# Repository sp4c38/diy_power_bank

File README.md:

# DIY Power Bank

This repository contains the project files for my custom power bank, including the PCB design and fabrication files, firmware, iOS app, and 3D-printable enclosure parts.

The files are provided for anyone interested in the project or who wants to learn from it. This is not a complete step-by-step build guide.

[Project showcase](https://www.space8.me/custom-power-bank.html)

Lithium-ion batteries can be dangerous. The files are provided as-is and should only be used with appropriate knowledge and safety precautions.

## License

This project is available under the [MIT License](LICENSE).

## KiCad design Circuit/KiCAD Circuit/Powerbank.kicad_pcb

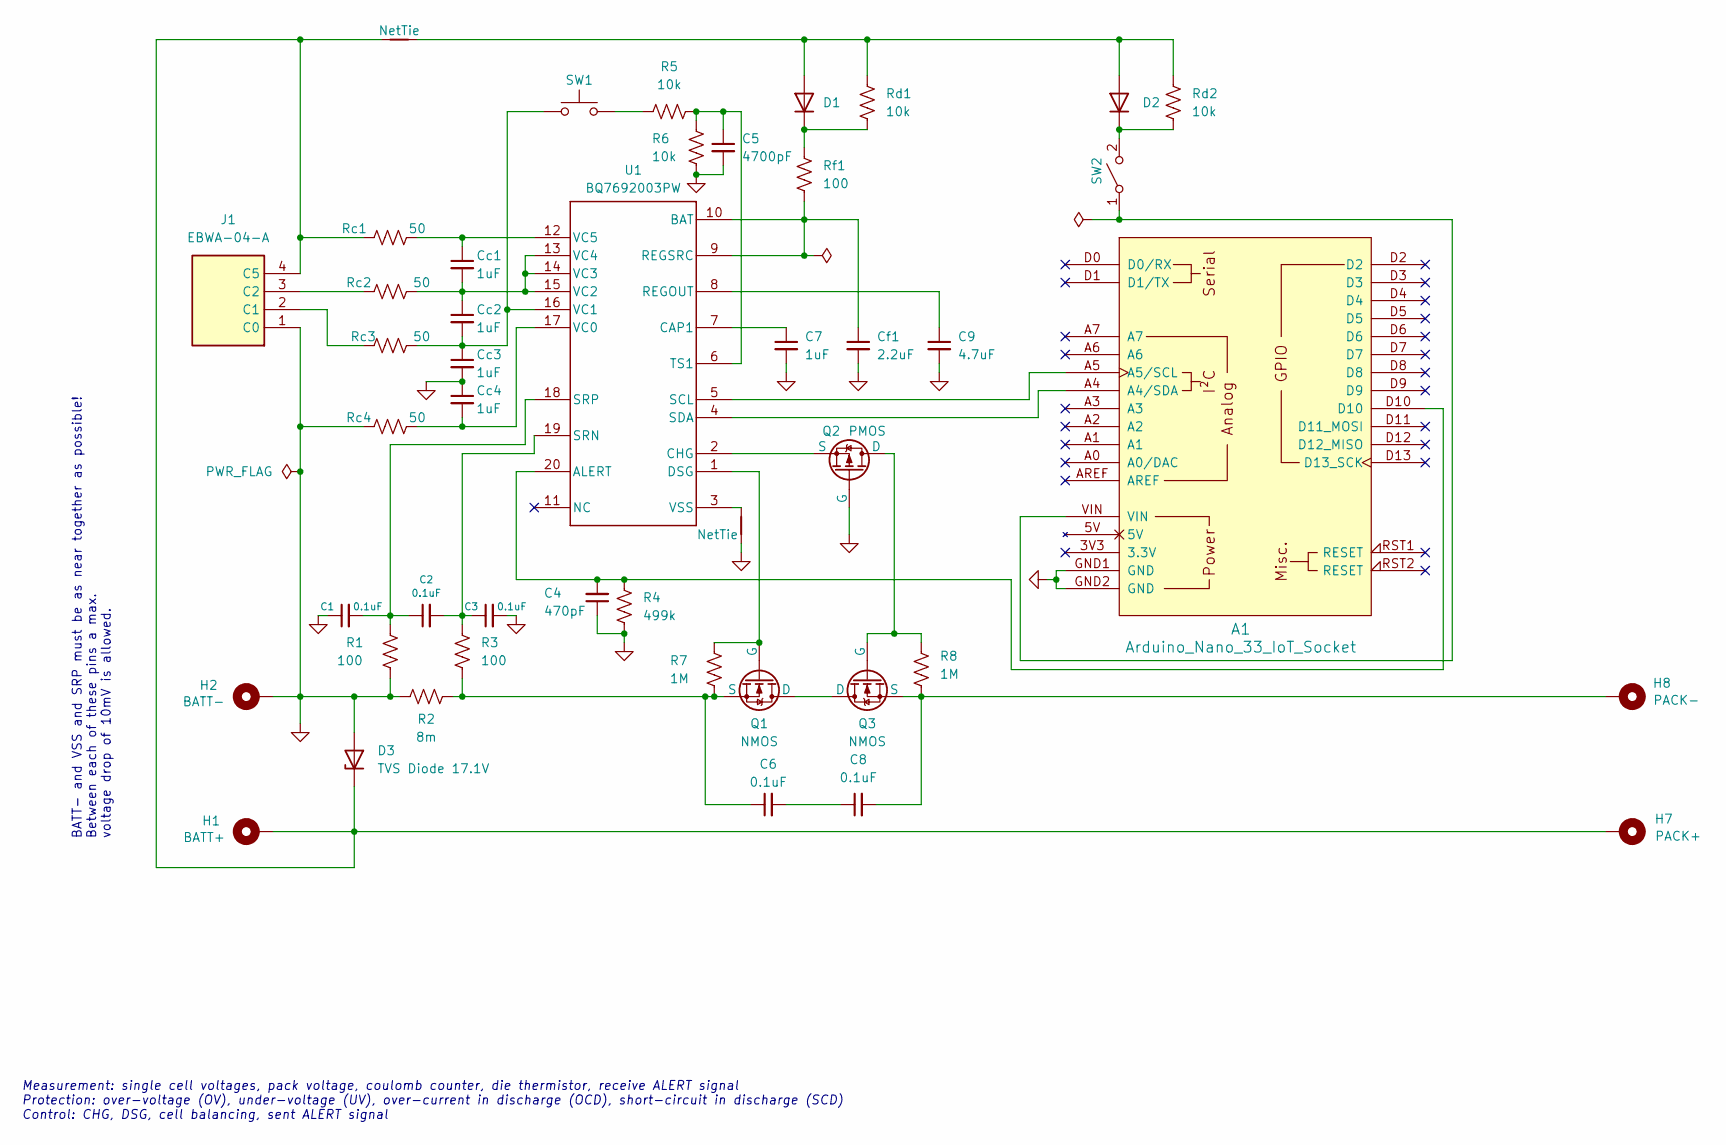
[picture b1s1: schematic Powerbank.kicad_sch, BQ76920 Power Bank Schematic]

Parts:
A1: Arduino_Nano_33_IoT_Socket
C1, C2, C3, C6, C8: 0.1uF; K104K10X7RF53H5_VIS; Mouser 594-K104K10X7RF53H5
C4: 470pF; K471K10X7RF5UH5_VIS; Mouser 594-K471K10X7RF5UH5
C5: 4700pF; CAP_C410C_AX_X7R_AXIMAX_KEM; Mouser 80-C410C472K1R
C7: 1uF; K105K20X7RF5TH5_VIS; Mouser 594-K105K20X7RF5TH5
C9: 4.7uF; CAP_FG24_TDK; Mouser 810-FG24X7R1E475KRT6
Cc1, Cc2, Cc3, Cc4: 1uF; K105K20X7RF5TH5_VIS; Mouser 594-K105K20X7RF5TH5
Cf1: 2.2uF; CAP_FG18_TDK; Mouser 810-FG18X5R1E225KRT6
D1, D2: D; 1N4149TR; Mouser 512-1N4149
D3: TVS Diode 17.1V; D_DO-41_SOD81_P7.62mm_Horizontal; Mouser 576-P4KE20A
H1: BATT+; Power Connection Pads
H2: BATT-; Power Connection Pads
H7: PACK+; Power Connection Pads
H8: PACK-; Power Connection Pads
J1: EBWA-04-A; Manufacturer_Part_Number EBWA-04-A; Mouser 737-EBWA-04-A
NT1, NT2: NetTie; NetTie General Net Class
Q1, Q3: NMOS; IRLB4132PBF; Mouser 942-IRLB4132PBF
Q2: PMOS; TO-92_MC_MCH; Mouser 689-VP3203N3-G
R1, R3: 100; STA_RNF14_STP; Mouser 708-RNF14FTD100R
R2: 8m; RES_14A_OHM; Mouser 588-14AFR008E
R4: 499k; YAG_MF25_YAG; Mouser 603-MFR-25FBF52-499K
R5, R6: 10k; STA_RNF18_STP; Mouser 708-RNF18FTD10K0
R7, R8: 1M; YAG_MF25_YAG; Mouser 603-MFR-25FRF521M
Rc1, Rc2, Rc3, Rc4: 50; RES_CMF07_VIS; Mouser 71-CMF5550R000FKEK70
Rd1, Rd2: 10k; STA_RNF18_STP; Mouser 708-RNF18FTD10K0
Rf1: 100; STA_RNF14_STP; Mouser 708-RNF14FTD100R
SW1: SW_Push; Switch Pads
SW2: SW_SPST; Switch Pads
U1: BQ7692003PW; PW0020A_N; Mouser 595-BQ7692003PW

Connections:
GND: A1.GND1 (GND), A1.GND2 (GND), C1.1, C3.2, C4.1, C5.2, C7.2, C9.2, Cc3.2, Cc4.1, Cf1.2, D3.2 (A), H2.1, J1.1 (C0), NT2.1, Q2.2 (G), R1.2, R2.1, R4.2, R6.2, Rc4.1
unnamed: A1.A4 (A4/SDA), U1.4 (SDA)
unnamed: A1.A5 (A5/SCL), U1.5 (SCL)
unnamed: C6.2, C8.1
unnamed: D1.2 (A), D2.2 (A), NT1.2, Rd1.1, Rd2.1
unnamed: D1.1 (K), Rd1.2, Rf1.1
unnamed: D2.1 (K), Rd2.2, SW2.2 (B)
unnamed: D3.1 (K), H1.1, H7.1, J1.4 (C5), NT1.1, Rc1.1
unnamed: J1.2 (C1), Rc3.1
unnamed: J1.3 (C2), Rc2.1
unnamed: Q1.1 (D), Q3.1 (D)
unnamed: Q1.2 (G), R7.1, U1.1 (DSG)
unnamed: C6.1, Q1.3 (S), R2.2, R3.2, R7.2
unnamed: Q2.1 (D), Q3.2 (G), R8.1
unnamed: Q2.3 (S), U1.2 (CHG)
unnamed: C8.2, H8.1, Q3.3 (S), R8.2
unnamed: R5.1, SW1.2
unnamed: A1.VIN, SW2.1 (A)
unnamed: A1.D10, C4.2, R4.1, U1.20 (ALERT)
unnamed: Cf1.1, Rf1.2, U1.9 (REGSRC), U1.10 (BAT)
unnamed: C7.1, U1.7 (CAP1)
unnamed: C9.1, U1.8 (REGOUT)
unnamed: C2.2, C3.1, R3.1, U1.19 (SRN)
unnamed: C1.2, C2.1, R1.1, U1.18 (SRP)
unnamed: C5.1, R5.2, R6.1, U1.6 (TS1)
unnamed: Cc4.2, Rc4.2, U1.17 (VC0)
unnamed: Cc2.2, Cc3.1, Rc3.2, SW1.1, U1.16 (VC1)
unnamed: Cc1.2, Cc2.1, Rc2.2, U1.13 (VC4), U1.14 (VC3), U1.15 (VC2)
unnamed: Cc1.1, Rc1.2, U1.12 (VC5)
unnamed: NT2.2, U1.3 (VSS)

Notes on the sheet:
BATT- and VSS and SRP must be as near together as possible! Between each of these pins a max. voltage drop of 10mV is allowed.
Measurement: single cell voltages, pack voltage, coulomb counter, die thermistor, receive ALERT signal Protection: over-voltage (OV), under-voltage (UV), over-current in discharge (OCD), short-circuit in discharge (SCD) Control: CHG, DSG, cell balancing, sent ALERT signal

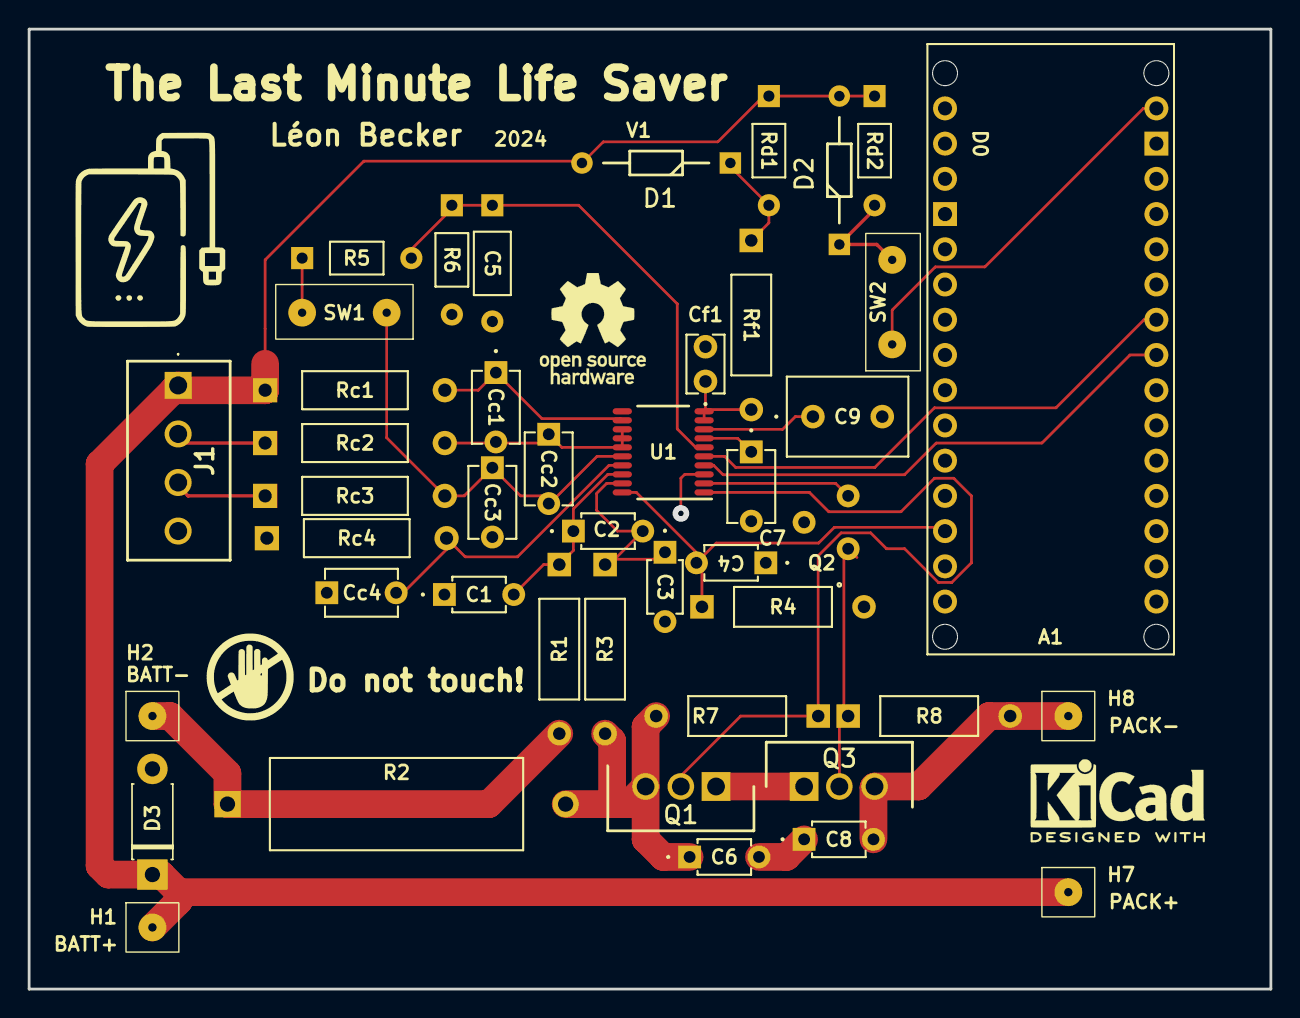
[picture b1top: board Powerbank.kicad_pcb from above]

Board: 2 copper layers, 89.5 x 69.2 mm, 49 parts (0 on the bottom side), 30 nets.

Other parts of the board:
G1: LOGO; Do Not Touch Symbol
G2: OSHW-Logo_7.5x8mm_SilkScreen
REF1: KiCad-Logo2_5mm_SilkScreen

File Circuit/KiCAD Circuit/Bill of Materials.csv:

"Reference","Value","Footprint","Qty","DNP","Mouser"
"A1","Arduino_Nano_33_IoT_Socket","Arduinos:Arduino_Nano_33_IoT_Socket","1","",""
"C1,C2,C3,C6,C8","0.1uF","K104K10X7RF53H5:K104K10X7RF53H5_VIS","5","","594-K104K10X7RF53H5"
"C4","470pF","K471K10X7RF5UH5:K471K10X7RF5UH5_VIS","1","","594-K471K10X7RF5UH5"
"C5","4700pF","C410C472K1R5TA:CAP_C410C_AX_X7R_AXIMAX_KEM","1","","80-C410C472K1R"
"C7,Cc1,Cc2,Cc3,Cc4","1uF","K105K20X7RF5TH5:K105K20X7RF5TH5_VIS","5","","594-K105K20X7RF5TH5"
"C9","4.7uF","FG24X7R1E475KRT06:CAP_FG24_TDK","1","","810-FG24X7R1E475KRT6"
"Cf1","2.2uF","FG18X5R1E225KRT06:CAP_FG18_TDK","1","","810-FG18X5R1E225KRT6"
"D1,D2","D","Custom Footprints:1N4149TR","2","","512-1N4149"
"D3","TVS Diode 17.1V","Diode_THT:D_DO-41_SOD81_P7.62mm_Horizontal","1","","576-P4KE20A"
"H1","BATT+","Custom Footprints:Power Connection Pads","1","",""
"H2","BATT-","Custom Footprints:Power Connection Pads","1","",""
"H7","PACK+","Custom Footprints:Power Connection Pads","1","",""
"H8","PACK-","Custom Footprints:Power Connection Pads","1","",""
"J1","EBWA-04-A","Custom Footprints:EBWA-04-A","1","","737-EBWA-04-A"
"Q1,Q3","NMOS","Custom Footprints:IRLB4132PBF","2","","942-IRLB4132PBF"
"Q2","PMOS","Custom Footprints:TO-92_MC_MCH","1","","689-VP3203N3-G"
"R1,R3,Rf1","100","RNF14FTD100R:STA_RNF14_STP","3","","708-RNF14FTD100R"
"R2","8m","14AFR008E:RES_14A_OHM","1","","588-14AFR008E"
"R4","499k","MFR-25FBF52-499K:YAG_MF25_YAG","1","","603-MFR-25FBF52-499K"
"R5,R6,Rd1,Rd2","10k","RNF18FTD10K0:STA_RNF18_STP","4","","708-RNF18FTD10K0"
"R7,R8","1M","MFR-25FRF52-1M:YAG_MF25_YAG","2","","603-MFR-25FRF521M"
"Rc1,Rc2,Rc3,Rc4","50","CMF5550R000FKEK70:RES_CMF07_VIS","4","","71-CMF5550R000FKEK70"
"SW1","SW_Push","Custom Footprints:Switch Pads","1","",""
"SW2","SW_SPST","Custom Footprints:Switch Pads","1","",""
"U1","BQ7692003PW","BQ7692003PW:PW0020A_N","1","","595-BQ7692003PW"

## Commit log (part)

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2023-12-29 Backup
2024-03-12 Ordered
2024-03-31 Fixed use of keyword "register"
2024-04-01 Backup 2
2024-04-01 Added CRC
2024-04-05 Added many software features (wip)
2024-04-11 Added balancing algorithm
2024-04-17 Backup (PlatformIO)
2024-06-26 Changed limits
2024-09-23 Small improvements
2024-09-24 Added constant voltage charging.
2024-09-26 Changed balancing settings
2026-06-26 Added .gitignore
2026-06-26 Restructured project and added firmware hardware map
2026-06-26 Restructured code folder
2026-06-26 Added help, status, ... commands to see state of powerbank
2026-06-26 Reworked power bank firmware.
    Does the same, but better.
2026-06-26 Added power bank app
2026-06-26 Improved app UI
